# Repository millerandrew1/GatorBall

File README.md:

# GatorBall

# Sprint 1 10/8/2024 to 10/25/2024: Pre-Alpha Build
Work Completed: 
  This sprint we focuses on the front end of our design. We worked on showing dummy data and making the program that the referee will be using when determining the position of the football. We created a client that would act as our "football" and that would connect to a server and send dummy data which represents the distance from the anchor points. Then we have a python script called ble_triangulate.py that does the calculation of the exact position of the client and then we output that to our UI which displays the data. 

  We received our ESP-32 and DW3000 on Thursday the day before the Pre-Alpha was due so we did not have time to write a lot of code but we did have resources that we previously found and used that code to test our microchips. We were successfully able to send and receive data between the two chips and the data was the distance between the two microchips. In the future we will add the third DW3000 which will act as the football and it will take in the distance between the two microchips and then it will send that data to the ble_triangulate to calculate the position of the ball.

# Sprint 2 10/26/2024 to 11/22/2024: Prototype Design
This sprint we focued on getting the data from our tag to print to the UI. We tried to use another DW3000 to be the football but due to issues with Ardunio and there not being a compatible library we are sticking with the 1 anchor point and 1 tag for the prototype. The tag takes data from the anchor point through UWB and then is connected through bluetooth to our UI using a COM Port where we display the distance from the tag from the anchor point on the football field. We also have it continuously send data through the bluetooth so that every few miliseconds it gets new data and updates the UI. Also when the tag moves it is shown on the UI as a football moving on the field. 

Future plans for next sprint involve trying to incorporate a second anchor point so we can get a 2D position field instead of the 1D field we have now. We also need to make a PCB with the DW3000 and the ESP-32 along with including a power source. This will then need to be incorporated into a football. We also plan on transferring our python UI into a react application in order to make the project accessable for apps to be able to use it. Along with that we want to make our UI more interactable which will take in more inputs like line of scrimmage, first down line, and other various things involved in a football game (score, team names, clock time). We also have a football moving on the screen but we want to be able to visually show the line of scrimmage and the first down line.  

# Sprint 3 1/13/2025 to 1/30/2025: Alpha Build
This sprint we focused on several things in order to maximize our productivity. First we started working on the PCB that will go into the football and we are designing it on KiCad. We also ordered another anchor point to use as testing for our two anchor point postion triangulation. For our beta build if our PCB is not ready we want to use this extra anchor point as the football so we can start writing the code for it.  Next we updated our UI to be able to take in inputs and have the first down and line of scrimmage lines move depending on where the user wants the lines to be placed. We also are trying to use react to be able to host the program instead of python.

# Sprint 4 1/31/2025 to 2/21/2025: Beta Build
This sprint we continued to add features to the UI. We allowed the user to select which side of the field the line of scrimmage and first down markers were. We also made the lines scaled better and we created a formula to make the football move to scale as it would on a real field. We designed our PCB and ordered it and continued to wrok on the React application. We also designed and printed pylons for the anchor points. 

# PROCESS FOR RUNNING CODE AND CONNECTING BLUETOOTH TO PC

First go to src/hardware/range_rx and upload that Arduino code to one of the DW3000 ESP 32 modules. That is now the tag. Then in src/hardware/range_tx upload that to the other one and that is your anchor point. They should now be sending data to each other and the tag should be serial printing the distance. To connect the tag to the bluetooth go to bluetooth settings and scroll down and click devices then in there click more bluetooth settings. In there click the tab that says COM PORTS and click add and add the ESP_32. Take note of what COM Port it is connected to. Finally go to src/FrontEnd/ui.py. Change line 44 to reflect what COM port the bluetooth is transmitting through. Then, open PUTTY or any other application used to connect to serial ports. Connect to the COM port you recorded and use a baud rate of 115200. Ensure that you can see data coming in over the serial port terminal. If so, close the serial port terminal. You are now ready to run the application. Execute "python ui.py" and you should see data printing to the UI as well as the position of the ball changing on screen. To identofy we named the two anchor points the one with the short cord is 12.

# BUGS

Bluetooth and UWB, like many other wireless protocols, are finicky. Throughout our design process, we have encountered many situations where connecting to the ESP32 tag that we will be putting into a football over Bluetooth has been unreliable and difficult to get working at times. Furthermore, after testing the UWB capabilities of the DWM3000 modules, we’ve discovered that it is prone to interference from physical obstructions like walls and even people as the transmission of data is impeded by these effects. Our workaround to these issues for the purpose of the prototype has been to disconnect and reconnect to the Bluetooth device as well as maintaining “line of sight” for the two ESP32s communicating over UWB. Also, we check to ensure that the data we are receiving is of the valid format (i.e., a numerical float value). We have determined that at this time, so long as the proper preparations have been made, there is currently no need for any other error correction or recovery mechanisms for the prototype. However, in the future, we would like to implement an Automatic Repeat Request (ARQ) system for 1) the device communicating with the tag over Bluetooth and 2) the tags and anchors communicating over UWB. This will assist in ensuring that instances of data are received correctly by the relevant devices and provide us with more precision with the real-time location tracking of the football. 

# DEPENDENCIES

Bleak BLE - https://github.com/hbldh/bleak 
Localization - https://github.com/kamalshadi/Localization
Localization dependency (may not be needed) - https://shapely.readthedocs.io/en/stable/

Installation commands
pip install localization
pip install bleak
pip install shapely

# Effort Log
Please disregard the effort log in this repo because you cannot see the comments made. The link for our effort log is here at this link below:
https://docs.google.com/spreadsheets/d/1YpcHQpgFyinJQXn12217S25mA8S0SkYA/edit?usp=sharing&ouid=113765046292722749022&rtpof=true&sd=true

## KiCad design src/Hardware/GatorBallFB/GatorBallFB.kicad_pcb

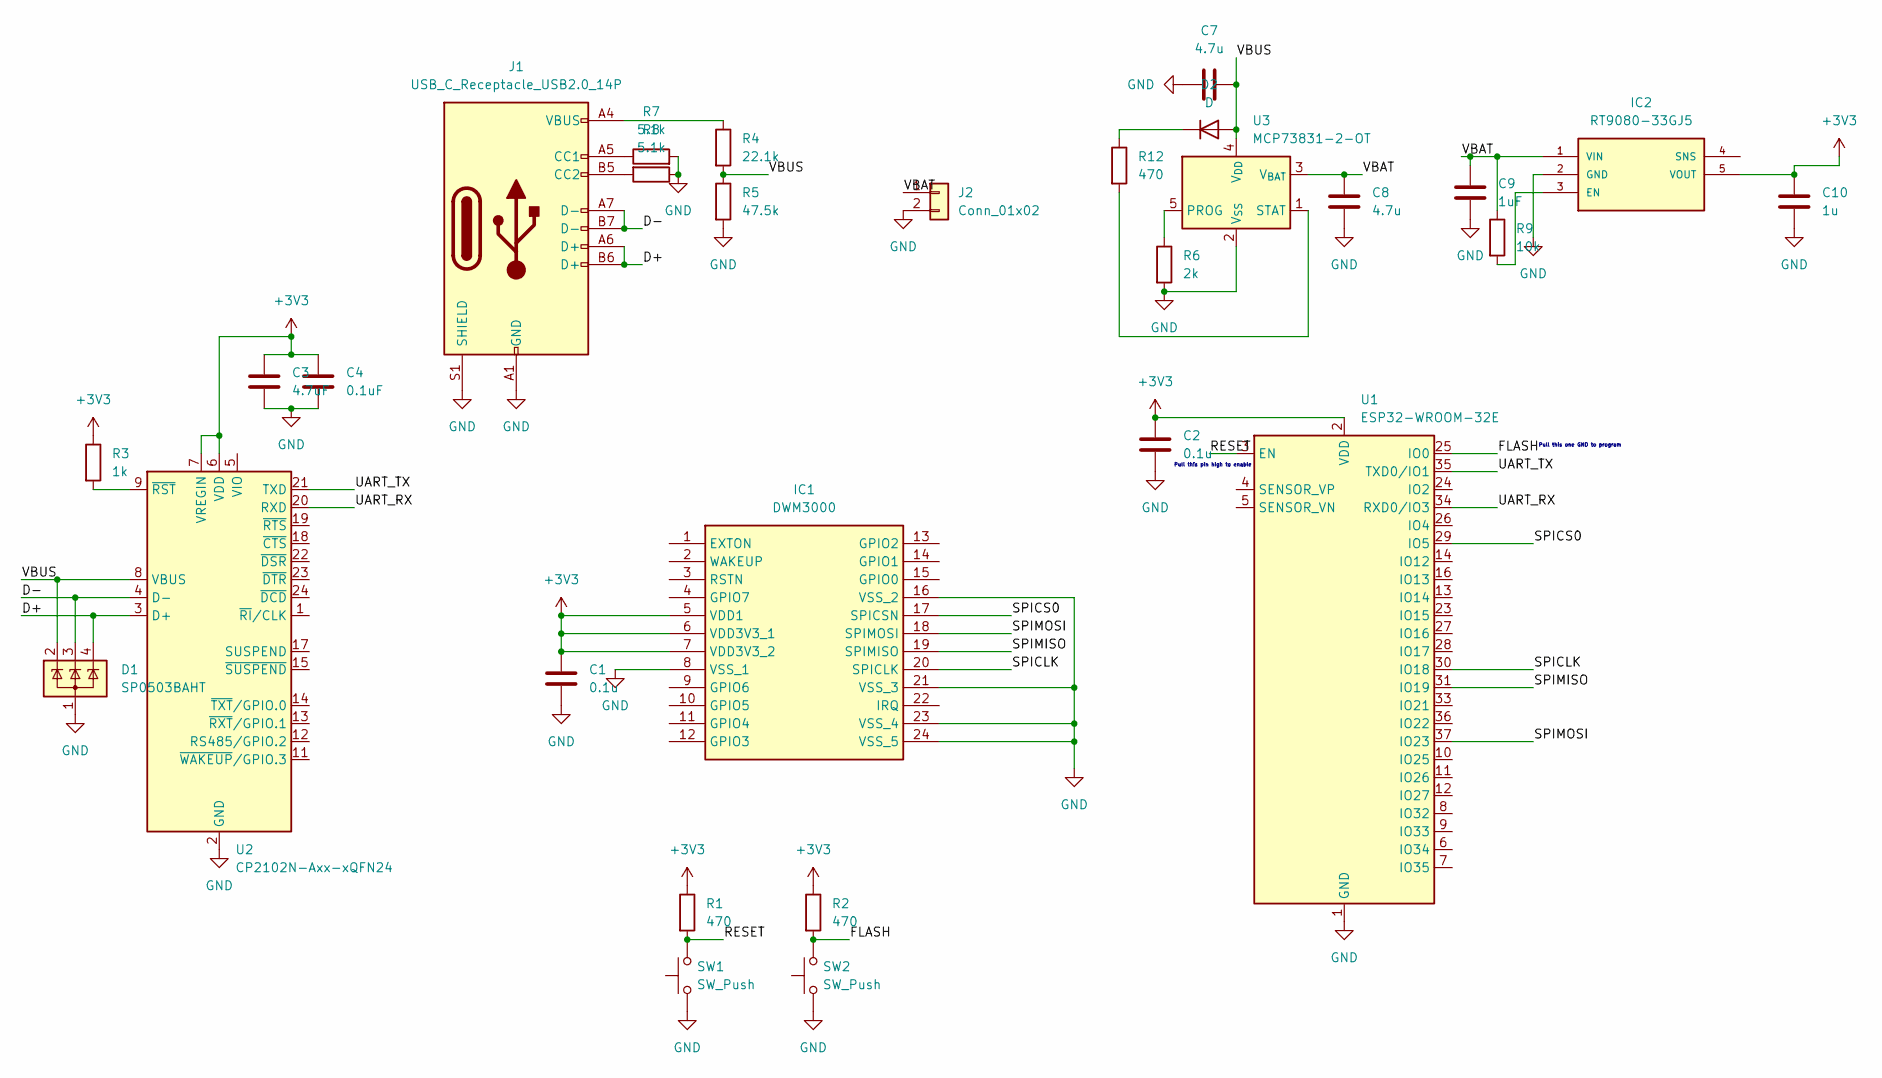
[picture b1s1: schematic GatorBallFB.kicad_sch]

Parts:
C1, C2: 0.1u; C_0201_0603Metric
C3: 4.7uF; C_0201_0603Metric
C4: 0.1uF; C_0201_0603Metric
C7, C8: 4.7u; C_0201_0603Metric
C9: 1uF; C_0201_0603Metric
C10: 1u; C_0201_0603Metric
D1: SP0503BAHT; SOT-143
D2: D; LED_0603_1608Metric
IC1: DWM3000; XCVR_DWM3000TR13; Manufacturer_Part_Number DWM3000; Mouser Part Number N/A
IC2: RT9080-33GJ5; SOT94P280X100-5N; Mouser_Part_Number 835-RT9080-33GJ5
J1: USB_C_Receptacle_USB2.0_14P; USB_C_Receptacle_GCT_USB4085
J2: Conn_01x02; JST_PH_B2B-PH-SM4-TB_1x02-1MP_P2.00mm_Vertical
R1, R2, R12: 470; R_0402_1005Metric
R3: 1k; R_0402_1005Metric
R4: 22.1k; R_0402_1005Metric
R5: 47.5k; R_0402_1005Metric
R6: 2k; R_0402_1005Metric
R7, R8: 5.1k; R_0402_1005Metric
R9: 10k; R_0402_1005Metric
SW1, SW2: SW_Push; SW_SPST_EVPBF
U1: ESP32-WROOM-32E; ESP32-WROOM-32D
U2: CP2102N-Axx-xQFN24; QFN-24-1EP_4x4mm_P0.5mm_EP2.6x2.6mm
U3: MCP73831-2-OT; SOT-23-5

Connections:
+3V3: C1.1, C2.1, C3.1, C4.1, C10.1, IC1.5 (VDD1), IC1.6 (VDD3V3_1), IC1.7 (VDD3V3_2), IC2.5 (VOUT), R1.1, R2.1, R3.1, U1.2 (VDD), U2.6 (VDD), U2.7 (VREGIN)
/D+: D1.4 (K), J1.A6 (D+), J1.B6 (D+), U2.3 (D+)
/D-: D1.3 (K), J1.A7 (D-), J1.B7 (D-), U2.4 (D-)
/FLASH: R2.2, SW2.2, U1.25 (IO0)
/RESET: R1.2, SW1.2, U1.3 (EN)
/SPICLK: IC1.20 (SPICLK), U1.30 (IO18)
/SPICS0: IC1.17 (SPICSN), U1.29 (IO5)
/SPIMISO: IC1.19 (SPIMISO), U1.31 (IO19)
/SPIMOSI: IC1.18 (SPIMOSI), U1.37 (IO23)
/UART_RX: U1.34 (RXD0/IO3), U2.20 (RXD)
/UART_TX: U1.35 (TXD0/IO1), U2.21 (TXD)
/VBAT: C8.1, C9.1, IC2.1 (VIN), J2.1, R9.1, U3.3 (V_{BAT})
/VBUS: C7.2, D1.2 (K), D2.2 (A), R4.2, R5.1, U2.8 (VBUS), U3.4 (V_{DD})
GND: C1.2, C2.2, C3.2, C4.2, C7.1, C8.2, C9.2, C10.2, D1.1 (A), IC1.8 (VSS_1), IC1.16 (VSS_2), IC1.21 (VSS_3), IC1.23 (VSS_4), IC1.24 (VSS_5), IC2.2 (GND), J1.A1 (GND), J1.A12 (GND), J1.B1 (GND), J1.B12 (GND), J1.S1 (SHIELD), J2.2, R5.2, R6.2, R7.2, R8.1, SW1.1, SW2.1, U1.1 (GND), U1.15 (GND), U1.38 (GND), U1.39 (GND), U2.2 (GND), U2.25 (GND), U3.2 (V_{SS})
unnamed: D2.1 (K), R12.1
unnamed: IC2.3 (EN), R9.2
unnamed: J1.A5 (CC1), R7.1
unnamed: J1.B5 (CC2), R8.2
unnamed: J1.A4 (VBUS), J1.A9 (VBUS), J1.B4 (VBUS), J1.B9 (VBUS), R4.1
unnamed: R3.2, U2.9 (~RST)
unnamed: R6.1, U3.5 (PROG)
unnamed: R12.2, U3.1 (STAT)

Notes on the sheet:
Pull this one GND to program
Pull this pin high to enable

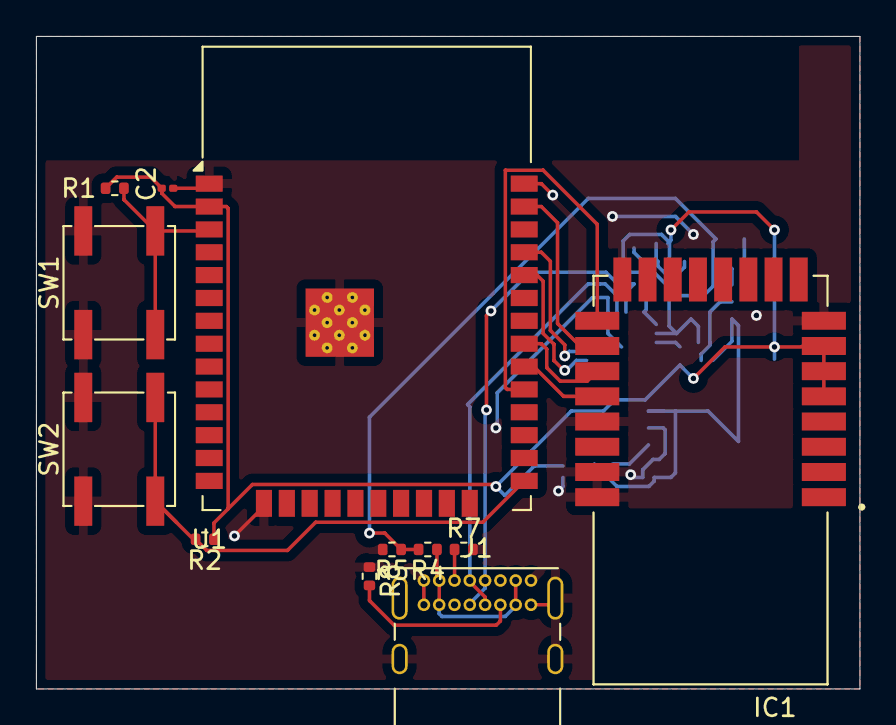
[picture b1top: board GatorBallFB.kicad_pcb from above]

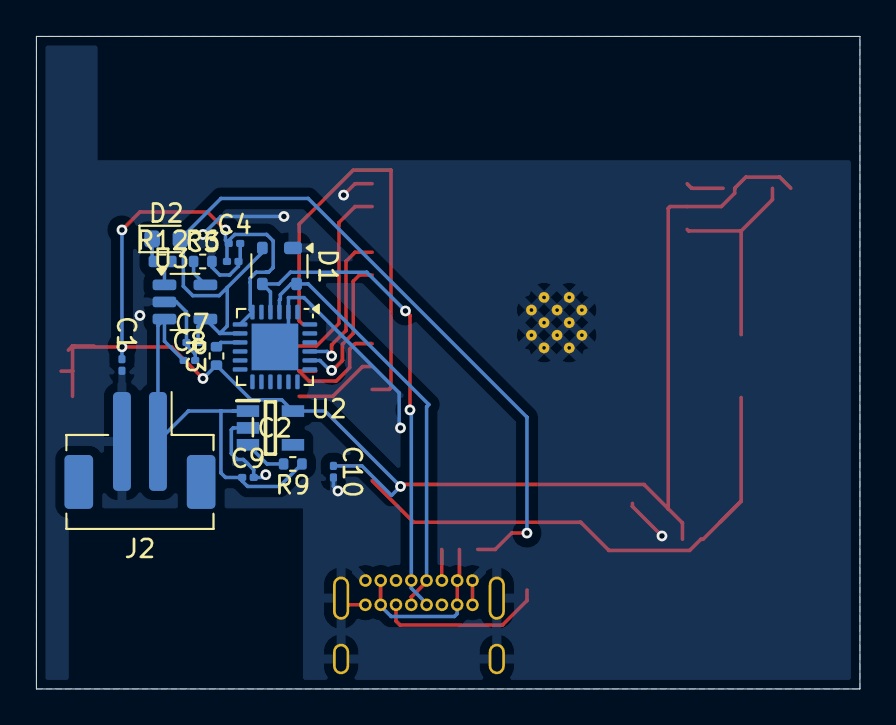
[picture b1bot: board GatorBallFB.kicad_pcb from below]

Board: 2 copper layers, 45.8 x 36.2 mm, 29 parts (17 on the bottom side), 22 nets.

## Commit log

2024-10-01 First commit for time tracking
2024-10-01 Purpose/need and short desc of artifact written, tentative
2024-10-01 Added timesheet along with the initial time added
2024-10-02 Added First draft of the draft schmatics
2024-10-02 Updating
2024-10-03 Updated time
2024-10-04 10/4/2024
2024-10-06 10/5/2024
2024-10-06 10/5/2024 Time Sheet
2024-10-06 Impact statement first draft
2024-10-07 Udated Draft Schmatics
2024-10-07 Added update to draft schmatic
2024-10-07 Update time sheet
2024-10-08 Added todays work
2024-10-08 10/8/2024
2024-10-08 Final Draft
2024-10-08 Final submission for design draft.
2024-10-08 Newest version of master timesheet. Recorded work time for meeting held on 10/8/2024.
2024-10-15 Added new times.
2024-10-22 Moved Design Draft
2024-10-22 Added DW3000
2024-10-22 New file for anchor
2024-10-22 Added file
2024-10-22 Added file structure
2024-10-22 Updated readme with dependecies
2024-10-22 Updated with mock updates for recalculating
2024-10-22 Created frontend. TODO: fix positioning of elements as they are a little messed up upon updating, rework updating function
2024-10-23 Added server example for potential demo since I couldn't find a solution for connecting with BLE
2024-10-23 Client for bluetooth example
2024-10-23 Added functions to better faciltate using server and client in other files
2024-10-24 Rename client.py to client_bt.py
2024-10-24 Rename server.py to server_bt.py
2024-10-24 Updated front end files for demo
2024-10-24 moved ui.py to frontend, removed Display dir
2024-10-24 Changes so that client waits to send before updates are made
2024-10-24 UI Text Fix
2024-10-24 Text Fix 2 UI
2024-10-24 Made ble_triangulate modular so it can be called in UI
2024-10-24 Added Y global variable
2024-10-24 UI connected to triangulate and recieving data from client
2024-10-24 Vendor examples to test boards
2024-10-24 Added second input
2024-10-24 Working demo, some things to clean up
2024-10-24 Added handshake to ensure client cannot sendinfo w/o server being ready
2024-10-24 fixed small error
2024-10-24 Demo video for frontend and bluetooth functionality
2024-11-05 Added bluetooth functionality
2024-11-07 added serial bluetooth to temp code
2024-11-08 serial reading in python
2024-11-12 11/12/2024 Effort Logs
2024-11-19 Added to UI
2024-11-20 Changed bluetooth
2024-11-20 UHHH
2024-11-20 Anchor
2024-11-20 added code to update lines on field, old version of UI
2024-11-20 New baseline for UI. Integrated UI with serial port to display current distance on UI. TODO: Implement features discussed in meeting 11/20/2024.
2024-11-20 Ball reflects distance of tag from anchor point (currently only one). Minor UI changes. TODO: Cosmetic improvements
2024-11-21 Update Anchor
2024-11-21 Update TAg
2024-11-22 Added BUGS section
2024-11-22 Updated positional parameters for demo
2025-01-21 Baseline/working state of project as of Jan 21, 2025. This build was used to present the prototype demonstration in the Fall '24 semester.
2025-01-21 pcb added
2025-01-21 ignore pycache. TODO: add pycache directory to .gitignore
2025-01-23 React Application
2025-01-23 PCB file upload (in progress
2025-01-28 updated PCB
2025-01-29 ui.py: Extensive changes for Alpha Build. Users can now input data into each field. First down marker and line of scrimmage lines will update dynamically on the UI based on user input. Added checks t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
2025-01-30 Create SchmaticFile
2025-01-30 ui.py: fixed off-center 50yd line bug
2025-01-30 Basic Implementation | Login Page and Placeholder Data Page
2025-01-31 3D model files for beta testing
2025-02-04 Football Field Update
2025-02-06 Added react to .gitignore list for cleanliness
2025-02-06 left/right buttons WIP
2025-02-06 reformatted ui, fixed positioning of lines, added left/right functionality
2025-02-10 schematic 99% complete
2025-02-13 Added automatic updates for yards to gain
2025-02-14 Implemented automatic yards to gain calculation and accounted for edge cases discussed during team meeting
2025-02-17 fully routed pcb
2025-02-18 Yardage Lines Fix
2025-02-19 Scoring Buttons
2025-02-20 broken code, saving here then reverting to baseline to fix
2025-02-20 Fixed code, two anchors are working. Further testing needed to determine validity of measurements being taken and must verify the coordinates being computed.
2025-02-20 Implemented support for two anchor points.
2025-03-06 User Interactivity
2025-03-06 Create test_code folder for depreciated code
2025-03-06 Rename src/FrontEnd/client_bt.py to src/FrontEnd/test_code/client_bt.py
2025-03-06 Rename src/FrontEnd/server_bt.py to src/FrontEnd/test_code/server_bt.py
2025-03-06 Create new folder for gator_Tag
2025-03-06 Create new folder for gator_anchor
2025-03-24 implementing moving average for smoothing out the distance values
2025-03-25 Implemented moving average filter to smooth out distance values. Found a suitable middle-ground between responsiveness and accuracy using ROLLING_SIZE=5
2025-03-27 Pylon design files
2025-03-27 Input Yardage/Flip Possession/Web Socket Server
2025-03-30 RC features
2025-04-02 removing files
2025-04-03 Re-Done React App with API and WebSocket Testing
2025-04-03 Game State API and Web Socket Implementation with Test Python Script
2025-04-08 changed ui.py: filtering inputs, export position history
2025-04-08 New Testing and Interactivity | Bug Fixes
2025-04-10 minor changes
2025-04-10 Testing
2025-04-11 working for new anchor positions reitz lawn
2025-04-13 React Update
2025-04-15 Final React Implementation
2025-04-15 Berndt -> main ui.py
2025-04-15 Add files via upload
    Final React Implementation
2025-04-15 test backend with C++
2025-04-15 React
2025-04-15 States
2025-04-17 Final Demo Updates
